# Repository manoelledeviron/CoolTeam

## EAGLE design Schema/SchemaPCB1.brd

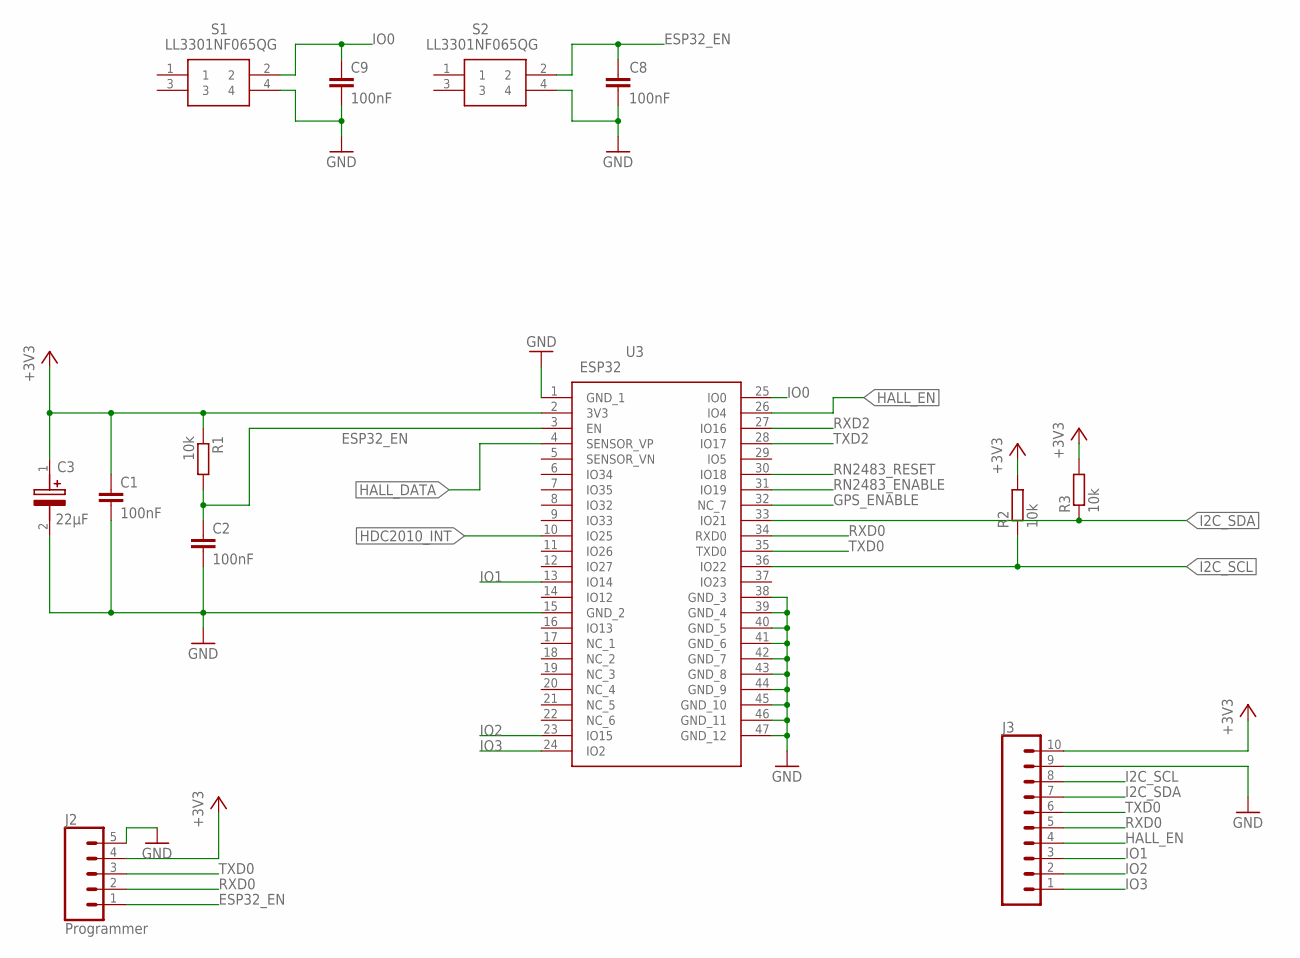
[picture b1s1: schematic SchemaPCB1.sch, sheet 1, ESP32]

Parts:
C1, C2, C8, C9: 100nF; C0805
C3: 22µF; CAPAE660X550N
J2: Programmer; 1X05
J3: CONN_10"; 1X10
R1: 10k; M0805
R2, R3: 10k; R0805
S1, S2: LL3301NF065QG
U3: ESP32; ESP32WROOM32EM113EH3200PH3Q0

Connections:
+3V3: C1.1, C3.1 (+), J2.4, J3.10, R1.1, R2.2, R3.2, U3.2 (3V3); also elsewhere on the board
ESP32_EN: C2.1, C8.2, J2.1, R1.2, S2.2, U3.3 (EN)
GND: C1.2, C2.2, C3.2 (-), C8.1, C9.2, J2.5, J3.9, S1.4, S2.4, U3.1 (GND_1), U3.15 (GND_2), U3.38 (GND_3), U3.39 (GND_4), U3.40 (GND_5), U3.41 (GND_6), U3.42 (GND_7), U3.43 (GND_8), U3.44 (GND_9), U3.45 (GND_10), U3.46 (GND_11), U3.47 (GND_12); also elsewhere on the board
GPS_ENABLE: U3.32 (NC_7); also elsewhere on the board
HALL_DATA: U3.4 (SENSOR_VP); also elsewhere on the board
HALL_EN: J3.4, U3.26 (IO4); also elsewhere on the board
HDC2010_INT: U3.10 (IO25); also elsewhere on the board
I2C_SCL: J3.8, R2.1, U3.36 (IO22); also elsewhere on the board
I2C_SDA: J3.7, R3.1, U3.33 (IO21); also elsewhere on the board
IO0: C9.1, S1.2, U3.25 (IO0)
IO1: J3.3, U3.13 (IO14)
IO2: J3.2, U3.23 (IO15)
IO3: J3.1, U3.24 (IO2)
RN2483_ENABLE: U3.31 (IO19); also elsewhere on the board
RN2483_RESET: U3.30 (IO18); also elsewhere on the board
RXD0: J2.2, J3.5, U3.34 (RXD0)
RXD2: U3.27 (IO16); also elsewhere on the board
TXD0: J2.3, J3.6, U3.35 (TXD0)
TXD2: U3.28 (IO17); also elsewhere on the board

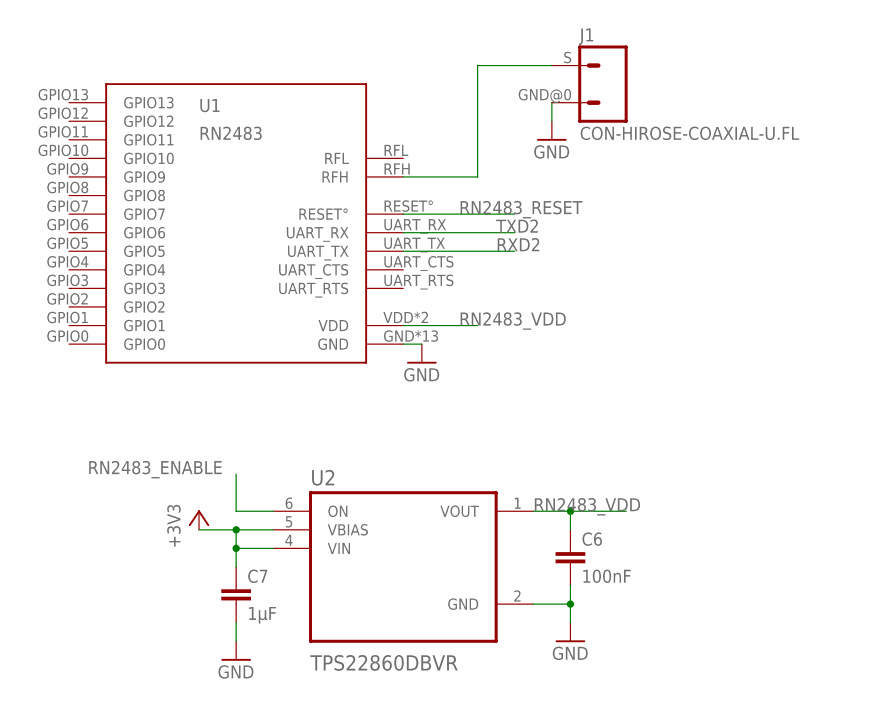
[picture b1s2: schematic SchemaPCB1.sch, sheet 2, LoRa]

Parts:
C6: 100nF; C0805
C7: 1µF; C0805
J1: CON-HIROSE-COAXIAL-U.FL; CON-U.FL
U1: RN2483
U2: TPS22860DBVR; SOT95P280X145-6N

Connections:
+3V3: C7.1, U2.4 (VIN), U2.5 (VBIAS); also elsewhere on the board
GND: C6.2, C7.2, J1.GND@0 (2), U1.GND, U1.GND1 (GND), U1.GND2 (GND), U1.GND3 (GND), U1.GND4 (GND), U1.GND5 (GND), U1.GND6 (GND), U1.GND7 (GND), U1.GND8 (GND), U1.GND9 (GND), U1.GND10 (GND), U1.GND11 (GND), U1.GND12 (GND), U2.2 (GND); also elsewhere on the board
unnamed: J1.S (1), U1.RFH
RN2483_ENABLE: U2.6 (ON); also elsewhere on the board
RN2483_RESET: U1.RESET°; also elsewhere on the board
RN2483_VDD: C6.1, U1.VDD, U1.VDD2 (VDD), U2.1 (VOUT)
RXD2: U1.UART_TX; also elsewhere on the board
TXD2: U1.UART_RX; also elsewhere on the board

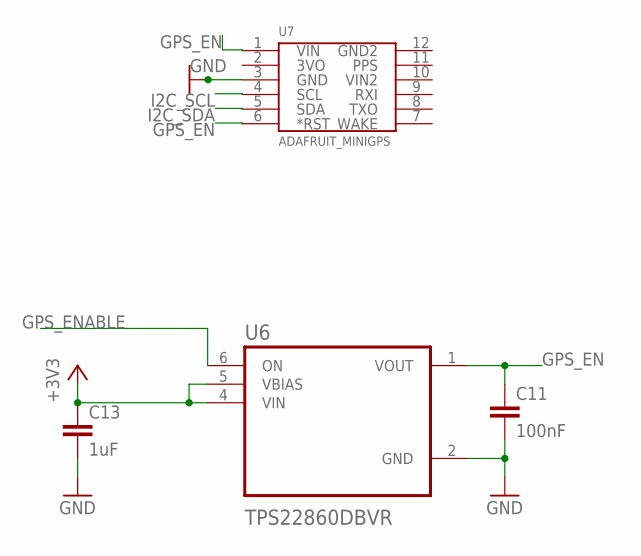
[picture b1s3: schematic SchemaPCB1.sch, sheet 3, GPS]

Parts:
C11: 100nF; C0805
C13: 1uF; C0805
U6: TPS22860DBVR; SOT95P280X145-6N
U7: ADAFRUIT_MINIGPS

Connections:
+3V3: C13.1, U6.4 (VIN), U6.5 (VBIAS); also elsewhere on the board
GND: C11.2, C13.2, U6.2 (GND), U7.3 (GND); also elsewhere on the board
GPS_EN: C11.1, U6.1 (VOUT), U7.1 (VIN), U7.6 (*RST)
GPS_ENABLE: U6.6 (ON); also elsewhere on the board
I2C_SCL: U7.4 (SCL); also elsewhere on the board
I2C_SDA: U7.5 (SDA); also elsewhere on the board

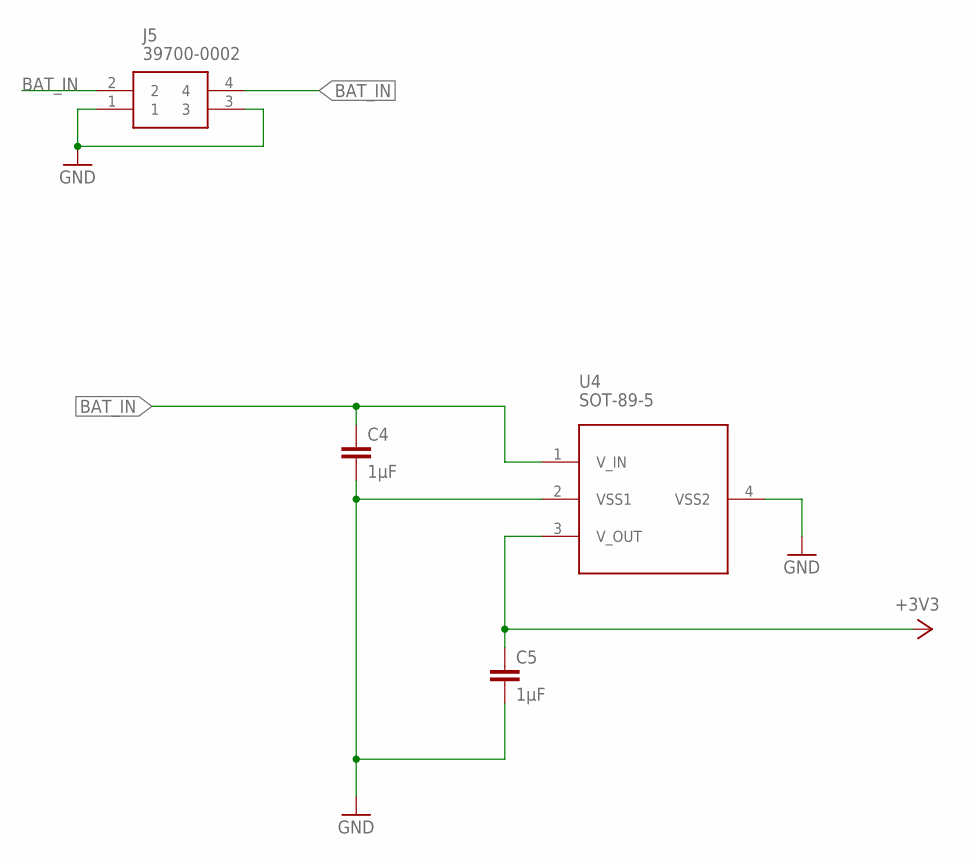
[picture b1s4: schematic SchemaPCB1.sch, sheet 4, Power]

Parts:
C4, C5: 1µF; C0805
J5: 39700-0002; 397000002
U4: SOT-89-5; SOT-89

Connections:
+3V3: C5.1, U4.3 (V_OUT); also elsewhere on the board
BAT_IN: C4.1, J5.2, J5.4, U4.1 (V_IN)
GND: C4.2, C5.2, J5.1, J5.3, U4.2 (VSS1), U4.4 (VSS2); also elsewhere on the board

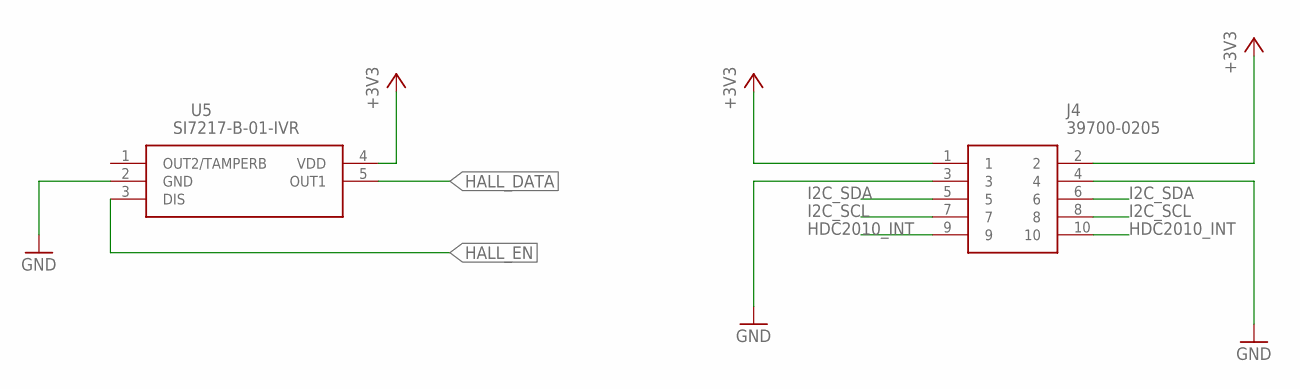
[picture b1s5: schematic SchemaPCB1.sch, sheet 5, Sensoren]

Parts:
J4: 39700-0205; 397000205
U5: SI7217-B-01-IVR; SOT95P275X125-5N

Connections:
+3V3: J4.1, J4.2, U5.4 (VDD); also elsewhere on the board
GND: J4.3, J4.4, U5.2 (GND); also elsewhere on the board
HALL_DATA: U5.5 (OUT1); also elsewhere on the board
HALL_EN: U5.3 (DIS); also elsewhere on the board
HDC2010_INT: J4.9, J4.10; also elsewhere on the board
I2C_SCL: J4.7, J4.8; also elsewhere on the board
I2C_SDA: J4.5, J4.6; also elsewhere on the board

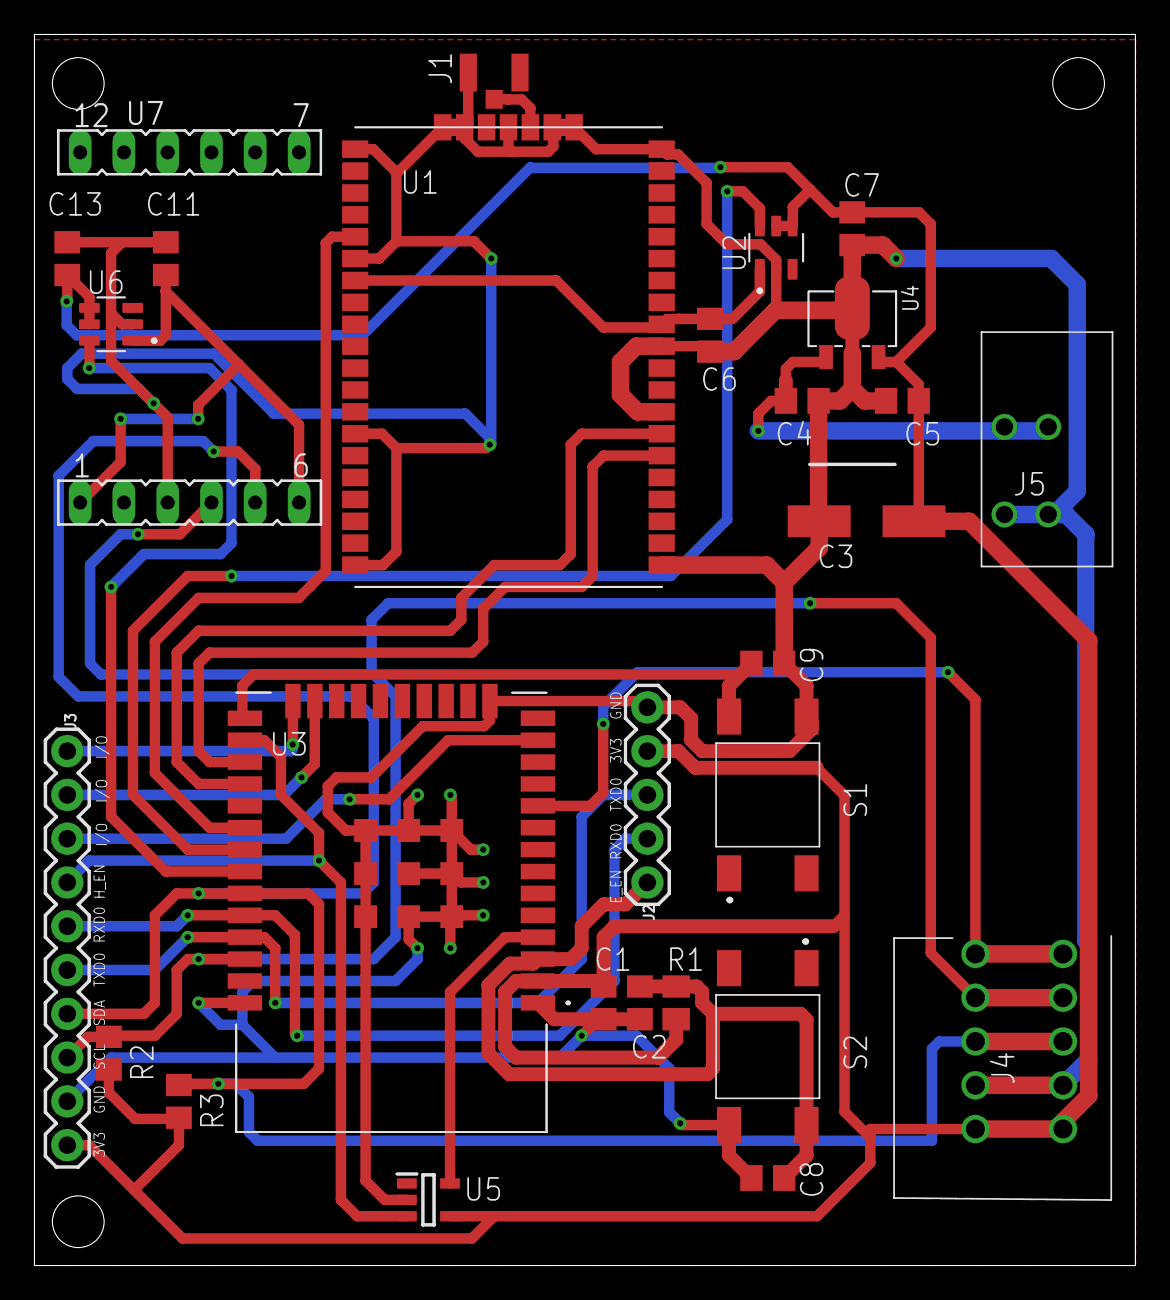
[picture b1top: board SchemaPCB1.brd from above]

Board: 2 copper layers, 63.9 x 71.4 mm, 28 parts (0 on the bottom side), 23 nets.

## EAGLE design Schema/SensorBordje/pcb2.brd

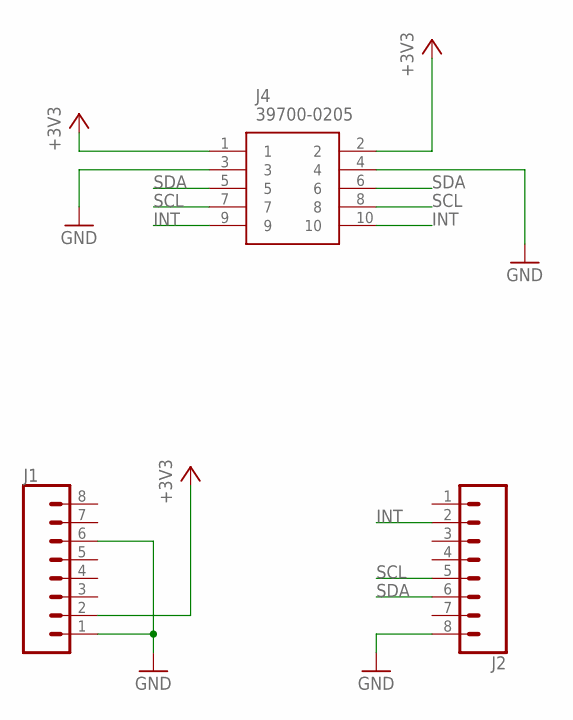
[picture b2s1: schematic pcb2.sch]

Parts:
J1, J2: CONN_08"; 1X08
J4: 39700-0205; 397000205

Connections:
+3V3: J1.2, J4.1, J4.2
GND: J1.1, J1.6, J2.8, J4.3, J4.4
INT: J2.2, J4.9, J4.10
SCL: J2.5, J4.7, J4.8
SDA: J2.6, J4.5, J4.6

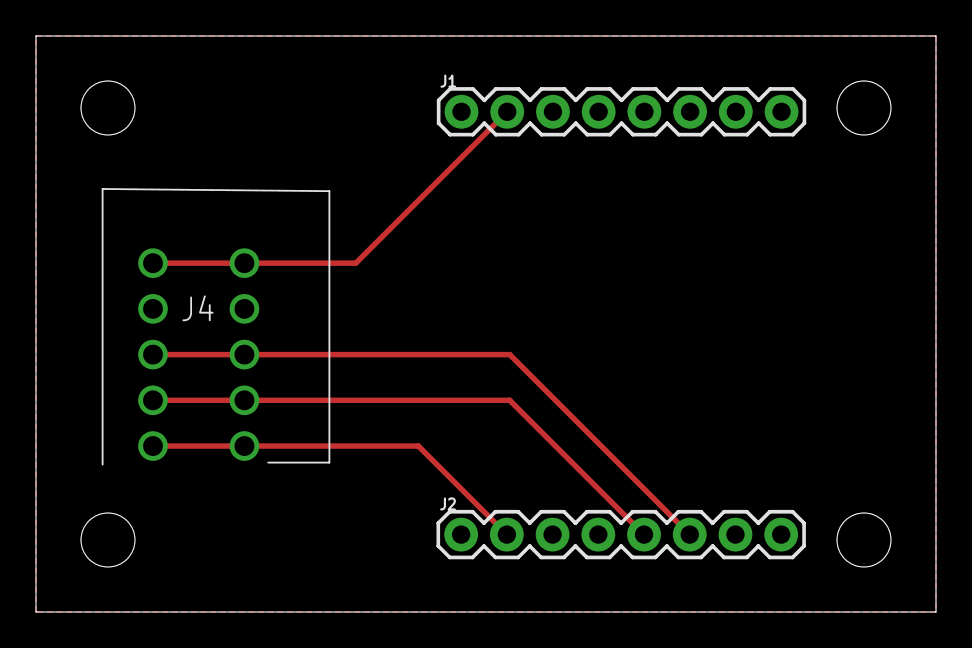
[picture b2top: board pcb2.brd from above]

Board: 2 copper layers, 50.0 x 32.0 mm, 3 parts (0 on the bottom side), 5 nets.

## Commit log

2021-03-15 planning en structuur toegevoegd
2021-03-15 Verslag1: Aanpak En Planning
2021-03-16 Update verslag 1
2021-03-16 aanpak naam veranderd
2021-03-16 planning en takenverdeling aangepast
2021-03-16 Structuur
2021-03-16 name change
2021-03-17 added few things
2021-03-17 hall datasheet added
2021-03-18 Schema + lib
2021-03-18 schema + pcb bom
2021-03-25 vsc project toegevoegd
2021-03-25 code documentatie
2021-03-25 Gemeten stromen
2021-03-26 LoRa toegevoegd
    RN2483 en power voorziening voor de RN2483 aangebracht op het schema
2021-03-26 Update BOM PCB.xlsx
    toevoegen componenten LoRa
2021-03-28 buck bom list added
2021-03-28 buck added (shcema en bom)
2021-03-29 schemaa
2021-03-31 LoRa schema afgewerkt
    Klaar voor board te maken
2021-03-31 schema dingen
2021-04-01 Board begonnen
2021-04-01 gps toegevoegd
2021-04-01 ferrite bead toegevoegd
2021-04-01 pull-up toegevoegd op I2C gps
2021-04-01 gps schema aangepast
2021-04-02 Bezig aan board
2021-04-02 mosfet symbool en footprint aangepast
2021-04-02 Eagle fix
    Board bijna klaar
2021-04-03 laatste componenten en pcb2 toegevoegd
2021-04-03 BOARD klaar
2021-04-03 gerbers added
2021-04-03 bom update
2021-04-03 BOM aangepast
2021-04-03 export zip
2021-04-07 aangepast om te gebruiken met gps breakout board
2021-04-07 gerber files geexporteerd
2021-04-08 export pcb1 aangepast, BOM PCB aangepast
2021-04-08 oude gerbers gedelete
2021-04-20 Code toegevoegd
    MQTT
    LoRa esp
    Data visualisatie
2021-05-03 main code Basile aangepast met GPS
2021-05-03 watchdog toegevoegd voor GPS
2021-05-03 data format gps data toegevoeg
2021-05-03 gps uit en variabelen aanpassen vooraleer esp in deepsleep mode gaat
2021-05-03 test code
2021-05-06 structuur schema aangepast
2021-05-06 code update
2021-05-08 schema's in pdf geexporteerd, code licht aangepast voor gps
2021-05-08 gps software lichtjes aangepast
2021-05-09 png files toegevoegd van pcbs
2021-05-09 data visualisatie afgewerkt
2021-05-10 code aangepast
2021-05-10 update main
2021-05-10 dingen
2021-05-11 code aangepast voor gps
2021-05-11 eidne labo
2021-05-15 datasheets
2021-05-18 verslag
2021-05-20 ontwerp schema toegevoegd voor verslag

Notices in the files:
parts and their libraries:
SparkFun-Connectors: Licensing: Creative Commons ShareAlike 4.0 International - https://creativecommons.org/licenses/by-sa/4.0
